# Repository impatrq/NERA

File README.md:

# N.E.R.A.

### Neuro Estimulación de Relajación Asistida

**Sistema de asistencia para la relajación mediante campos electromagnéticos pulsados (PEMF).**

=======
N.E.R.A.
Neuro Estimulación de Relajación Asistida
Sistema de asistencia para la relajación mediante campos electromagnéticos pulsados (PEMF).

N.E.R.A. - Sistema de asistencia para la relajación

¿Qué es N.E.R.A.?
N.E.R.A. es un dispositivo portátil en desarrollo, diseñado para explorar el uso de campos electromagnéticos pulsados (PEMF) como herramienta de apoyo para la relajación y el manejo del estrés.

El proyecto está orientado principalmente a personas que experimentan situaciones de estrés, sobrecarga mental o tensión. También se contemplan posibles aplicaciones relacionadas con el descanso y la recuperación física.

La propuesta consiste en integrar una vincha con bobinas electromagnéticas, un sistema electrónico de control y un reloj encargado del monitoreo. Estos componentes conforman un sistema que busca utilizar la información obtenida durante el monitoreo para gestionar el funcionamiento de la estimulación.

El desarrollo combina electrónica, programación y diseño mecánico con el objetivo de crear un dispositivo portátil, compacto y no invasivo.

## ¿Qué es N.E.R.A.?

N.E.R.A. es un dispositivo portátil en desarrollo, diseñado para explorar el uso de campos electromagnéticos pulsados (PEMF) como herramienta de apoyo para la relajación y el manejo del estrés.

El proyecto está orientado principalmente a personas que experimentan situaciones de estrés, sobrecarga mental o tensión. También se contemplan posibles aplicaciones relacionadas con el descanso y la recuperación física.

La propuesta consiste en integrar una vincha con bobinas electromagnéticas, un sistema electrónico de control y un reloj encargado del monitoreo. Estos componentes conforman un sistema que busca utilizar la información obtenida durante el monitoreo para gestionar el funcionamiento de la estimulación.

El desarrollo combina electrónica, programación y diseño mecánico con el objetivo de crear un dispositivo portátil, compacto y no invasivo.
=======
¿Cómo funciona?
El funcionamiento de N.E.R.A. se basa en la generación de campos electromagnéticos pulsados mediante bobinas.

El reloj realiza el monitoreo y se comunica con el microcontrolador ubicado en la vincha. El microcontrolador procesa la información recibida y gestiona el funcionamiento del sistema PEMF.

Cuando circula corriente eléctrica por las bobinas, se genera un campo magnético. Al modificar la corriente, el campo magnético también varía, produciendo pulsos electromagnéticos.

## ¿Cómo funciona?

El funcionamiento de N.E.R.A. se basa en la generación de campos electromagnéticos pulsados mediante bobinas.

El reloj realiza el monitoreo y se comunica con el microcontrolador ubicado en la vincha. El microcontrolador procesa la información recibida y gestiona el funcionamiento del sistema PEMF.

Cuando circula corriente eléctrica por las bobinas, se genera un campo magnético. Al modificar la corriente, el campo magnético también varía, produciendo pulsos electromagnéticos.

Las bobinas se encuentran ubicadas detrás de las orejas y forman parte del sistema de estimulación de la vincha.

El objetivo del proyecto es explorar la utilización de esta tecnología como herramienta de apoyo para favorecer la relajación y contribuir al bienestar del usuario.

---

## Arquitectura del sistema

N.E.R.A. está compuesto por diferentes módulos que trabajan de manera conjunta.

### 1. N.E.R.A. Headband — Vincha PEMF

=======
Las bobinas se encuentran ubicadas detrás de las orejas y forman parte del sistema de estimulación de la vincha.

El objetivo del proyecto es explorar la utilización de esta tecnología como herramienta de apoyo para favorecer la relajación y contribuir al bienestar del usuario.

Arquitectura del sistema
N.E.R.A. está compuesto por diferentes módulos que trabajan de manera conjunta.

1. N.E.R.A. Headband — Vincha PEMF

La vincha es el componente encargado de aplicar la estimulación electromagnética.

Incorpora dos bobinas rectangulares ubicadas detrás de las orejas y el microcontrolador encargado de gestionar el sistema.

Las bobinas generan campos magnéticos pulsados a partir de las señales eléctricas proporcionadas por el circuito de control.

El diseño mecánico contempla una estructura que permite alojar las bobinas y proteger los componentes electrónicos, manteniendo un formato portátil.

<<<<<<< Updated upstream

---

### 2. N.E.R.A. Watch — Sistema de monitoreo

=======
N.E.R.A. Headband

2. N.E.R.A. Watch — Sistema de monitoreo

El reloj es el componente destinado al monitoreo del usuario.

Su función dentro del proyecto es proporcionar información al sistema para permitir la gestión de la estimulación.

El reloj funciona de manera independiente de la vincha y cuenta con su propia alimentación eléctrica.

La comunicación entre el reloj y el microcontrolador de la vincha permite coordinar el funcionamiento de los distintos componentes del sistema.

---

### 3. Sistema PEMF

=======
N.E.R.A. Watch

3. Sistema PEMF

El sistema PEMF está compuesto principalmente por las bobinas y la electrónica necesaria para controlar su funcionamiento.

Las bobinas reciben señales eléctricas controladas por el sistema electrónico y generan campos electromagnéticos pulsados.

El sistema está diseñado para funcionar de forma no invasiva y se encuentra integrado físicamente en la vincha.

---

## Tecnología PEMF

PEMF (*Pulsed Electromagnetic Fields*) es una tecnología basada en la generación de campos electromagnéticos que varían mediante pulsos.
=======
Bobinas del sistema PEMF

Tecnología PEMF
PEMF (Pulsed Electromagnetic Fields) es una tecnología basada en la generación de campos electromagnéticos que varían mediante pulsos.

Su funcionamiento se relaciona con el principio de inducción electromagnética: cuando una corriente eléctrica circula por una bobina, genera un campo magnético. Al modificar esa corriente, el campo magnético también cambia.

La investigación sobre PEMF estudia la interacción de estos campos con los tejidos biológicos y sus posibles efectos en determinados procesos celulares.

Existen investigaciones sobre diferentes aplicaciones de esta tecnología, aunque sus efectos dependen de las características de la señal, la intensidad, la frecuencia y la aplicación estudiada.

En N.E.R.A., esta tecnología se utiliza como base para desarrollar un dispositivo orientado principalmente a la relajación y el manejo del estrés. Su eficacia para estos fines deberá evaluarse mediante pruebas específicas.

---

## Objetivos del proyecto

=======
Objetivos del proyecto

El objetivo principal de N.E.R.A. es desarrollar un dispositivo portátil que permita explorar la aplicación de campos electromagnéticos pulsados como herramienta de apoyo para la relajación.

Entre sus objetivos específicos se encuentran:

* Desarrollar un sistema PEMF compacto y portátil.
* Integrar la generación de campos electromagnéticos pulsados en una vincha.
* Implementar un sistema electrónico capaz de controlar el funcionamiento de las bobinas.
* Integrar un sistema de monitoreo mediante un reloj.
* Establecer comunicación entre el reloj y la electrónica de la vincha.
* Diseñar carcasas y soportes que permitan alojar y proteger los componentes.
* Fabricar prototipos mediante impresión 3D.
* Investigar las posibilidades de aplicación de la tecnología PEMF en el bienestar y la relajación.

---

## Desarrollo tecnológico

El proyecto integra distintas áreas de la ingeniería y el desarrollo tecnológico.

| Área            | Desarrollo                                                         |
| --------------- | ------------------------------------------------------------------ |
| Electrónica     | Diseño de circuitos, selección de componentes y desarrollo de PCB. |
| Firmware        | Programación del microcontrolador y control del sistema.           |
| Diseño mecánico | Modelado 3D de carcasas, soportes y alojamientos para las bobinas. |
| Impresión 3D    | Fabricación de piezas para el ensamblaje del dispositivo.          |
| Integración     | Conexión y coordinación de los diferentes módulos del sistema.     |

### Electrónica

=======
Desarrollar un sistema PEMF compacto y portátil.
Integrar la generación de campos electromagnéticos pulsados en una vincha.
Implementar un sistema electrónico capaz de controlar el funcionamiento de las bobinas.
Integrar un sistema de monitoreo mediante un reloj.
Establecer comunicación entre el reloj y la electrónica de la vincha.
Diseñar carcasas y soportes que permitan alojar y proteger los componentes.
Fabricar prototipos mediante impresión 3D.
Investigar las posibilidades de aplicación de la tecnología PEMF en el bienestar y la relajación.
Desarrollo tecnológico
El proyecto integra distintas áreas de la ingeniería y el desarrollo tecnológico.

Área	Desarrollo
Electrónica	Diseño de circuitos, selección de componentes y desarrollo de PCB.
Firmware	Programación del microcontrolador y control del sistema.
Diseño mecánico	Modelado 3D de carcasas, soportes y alojamientos para las bobinas.
Impresión 3D	Fabricación de piezas para el ensamblaje del dispositivo.
Integración	Conexión y coordinación de los diferentes módulos del sistema.
Electrónica

El diseño electrónico contempla una placa de circuito impreso que integra el microcontrolador y los componentes necesarios para controlar el sistema.

La distribución de los componentes y las conexiones se plantea teniendo en cuenta el tamaño del dispositivo, la alimentación y la disposición de las bobinas.

### Diseño mecánico

=======
PCB del sistema N.E.R.A.

Diseño mecánico

El diseño mecánico se centra en desarrollar una estructura que permita integrar los componentes de manera compacta y segura.

Se trabaja en el modelado de las carcasas de la placa electrónica, los alojamientos de las bobinas, separadores y soportes necesarios para el ensamblaje.

Las piezas se diseñan considerando su fabricación mediante impresión 3D.

---

## Tecnologías y herramientas

Las principales tecnologías y herramientas utilizadas en el desarrollo incluyen:

* **ESP32:** microcontrolador utilizado para gestionar el sistema electrónico.
* **C/C++:** programación del firmware.
* **Diseño de PCB:** desarrollo de circuitos electrónicos.
* **Blender:** modelado tridimensional de componentes y carcasas.
* **Impresión 3D:** fabricación de piezas mecánicas y prototipos.
* **GitHub:** almacenamiento, organización y seguimiento del desarrollo del proyecto.

---

## Estructura del repositorio

El repositorio está organizado para separar los distintos componentes del proyecto y facilitar su desarrollo.

| Directorio    | Contenido                                                |
| ------------- | -------------------------------------------------------- |
| `docs/`       | Documentación técnica, imágenes e informes del proyecto. |
| `firmware/`   | Código fuente y programas del microcontrolador.          |
| `hardware/`   | Esquemáticos, circuitos y diseños de PCB.                |
| `mechanical/` | Modelos 3D, carcasas, soportes y diseños mecánicos.      |

---

## Estado del proyecto

**En desarrollo.**
=======
Diseño mecánico de N.E.R.A.

Tecnologías y herramientas
Las principales tecnologías y herramientas utilizadas en el desarrollo incluyen:

ESP32: microcontrolador utilizado para gestionar el sistema electrónico.
C/C++: programación del firmware.
Diseño de PCB: desarrollo de circuitos electrónicos.
Blender: modelado tridimensional de componentes y carcasas.
Impresión 3D: fabricación de piezas mecánicas y prototipos.
GitHub: almacenamiento, organización y seguimiento del desarrollo del proyecto.
Estructura del repositorio
El repositorio está organizado para separar los distintos componentes del proyecto y facilitar su desarrollo.

Directorio	Contenido
docs/	Documentación técnica, imágenes e informes del proyecto.
firmware/	Código fuente y programas del microcontrolador.
hardware/	Esquemáticos, circuitos y diseños de PCB.
mechanical/	Modelos 3D, carcasas, soportes y diseños mecánicos.
Estado del proyecto
En desarrollo.

N.E.R.A. se encuentra en una etapa de diseño, desarrollo e integración de sus componentes electrónicos y mecánicos.

El proyecto contempla el desarrollo de prototipos, la integración de los sistemas y la realización de pruebas para evaluar su funcionamiento.

Las funcionalidades y aplicaciones previstas se irán documentando a medida que sean implementadas y validadas.

---

## Aplicaciones previstas

=======
Aplicaciones previstas

El proyecto se centra principalmente en investigar el uso de la tecnología PEMF como posible herramienta complementaria para favorecer la relajación y el bienestar.

También se consideran posibles aplicaciones relacionadas con el descanso y la recuperación física, incluidos contextos deportivos.

Estas aplicaciones forman parte de los objetivos de investigación y desarrollo del proyecto. N.E.R.A. no está validado como tratamiento para trastornos de salud mental ni sustituye la atención profesional.

---

## Institución

**Escuela de Educación Secundaria Técnica N.º 7 «Taller Regional Quilmes»**

Buenos Aires, Argentina.

**Proyecto:** N.E.R.A.
**Significado:** Neuro Estimulación de Relajación Asistida
**Área:** Aviónica y desarrollo tecnológico.

---

<p align="center">
  <strong>N.E.R.A. — Neuro Estimulación de Relajación Asistida.</strong>
</p>
=======
Institución
Escuela de Educación Secundaria Técnica N.º 7 «Taller Regional Quilmes»

Buenos Aires, Argentina.

Proyecto: N.E.R.A. Significado: Neuro Estimulación de Relajación Asistida Área: Aviónica y desarrollo tecnológico.

N.E.R.A. — Neuro Estimulación de Relajación Asistida.
>>>>>>> Stashed changes

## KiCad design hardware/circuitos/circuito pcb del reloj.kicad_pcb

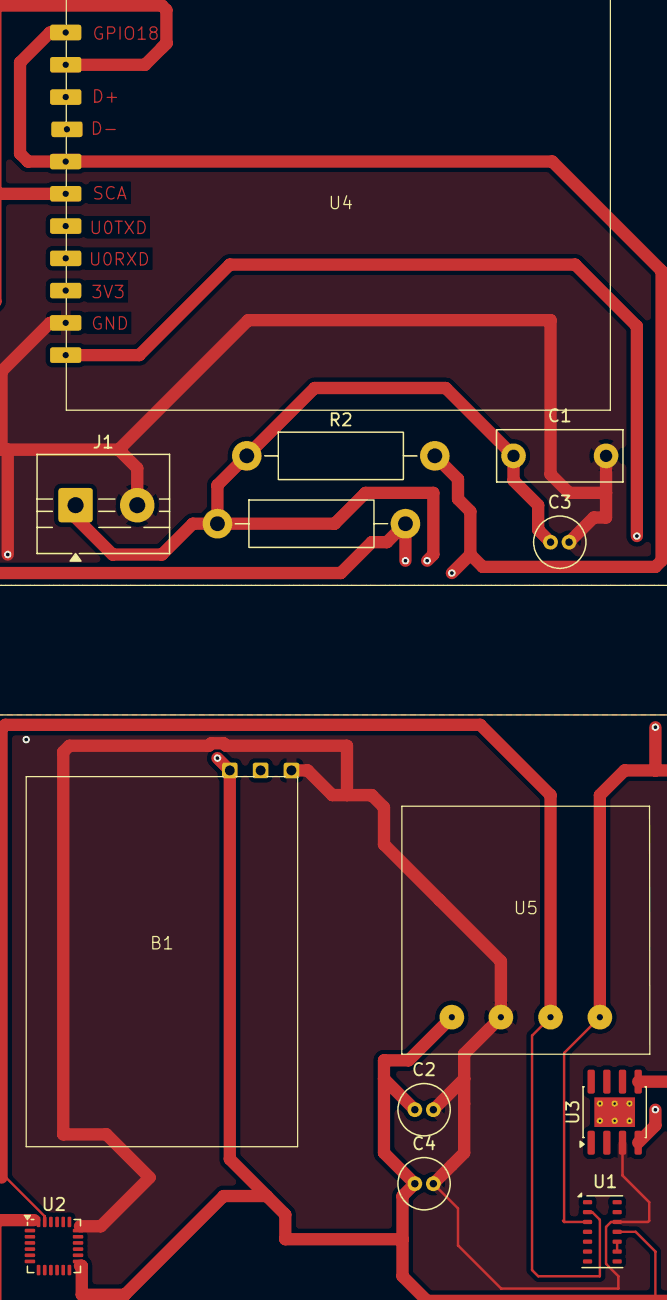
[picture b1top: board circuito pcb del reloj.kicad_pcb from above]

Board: 2 copper layers, 13 parts (0 on the bottom side), 6 nets.

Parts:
B1: batman 51
C1: 10uF; C_Rect_L10.0mm_W4.0mm_P7.50mm_FKS3_FKP3
C2, C3, C4: 100nF; C_Radial_D4.0mm_H5.0mm_P1.50mm
J1: Screw_Terminal_01x02; TerminalBlock_MaiXu_MX126-5.0-02P_1x02_P5.00mm
R1, R2: 4,7K; R_Axial_DIN0411_L9.9mm_D3.6mm_P15.24mm_Horizontal
U1: MAX30102; Maxim_OLGA-14_3.3x5.6mm_P0.8mm
U2: MPU-6050; InvenSense_QFN-24_4x4mm_P0.5mm
U3: TP4056-42-ESOP8; SOIC-8-1EP_3.9x4.9mm_P1.27mm_EP2.41x3.3mm_ThermalVias
U4: ESP32_C6
U5: Tito

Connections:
5v: U3.4 (V_{CC}), U4.11 (5V)
unnamed: U1.9 (VLED+), U1.10 (VLED+)
clock: R2.2, U1.2 (SCL), U2.23 (SCL), U4.1 (GPIO18), U4.5 (SCL), U5.3 (SCL)
dat sensor: R1.2, U1.3 (SDA), U2.24 (SDA), U4.2 (GPIO9), U4.6 (SDA), U5.4 (SDA)
prime: B1.1 (VCC), C1.1, C2.1, C3.1, C4.1, J1.1, R1.1, R2.1, U1.11 (VDD), U2.13 (VDD), U3.5 (BAT), U5.1 (VIN)
tierra: B1.3 (GND), C1.2, C2.2, C3.2, C4.2, J1.2, U1.12 (GND), U2.18 (GND), U3.3 (GND), U4.10 (GND), U5.2 (GND)

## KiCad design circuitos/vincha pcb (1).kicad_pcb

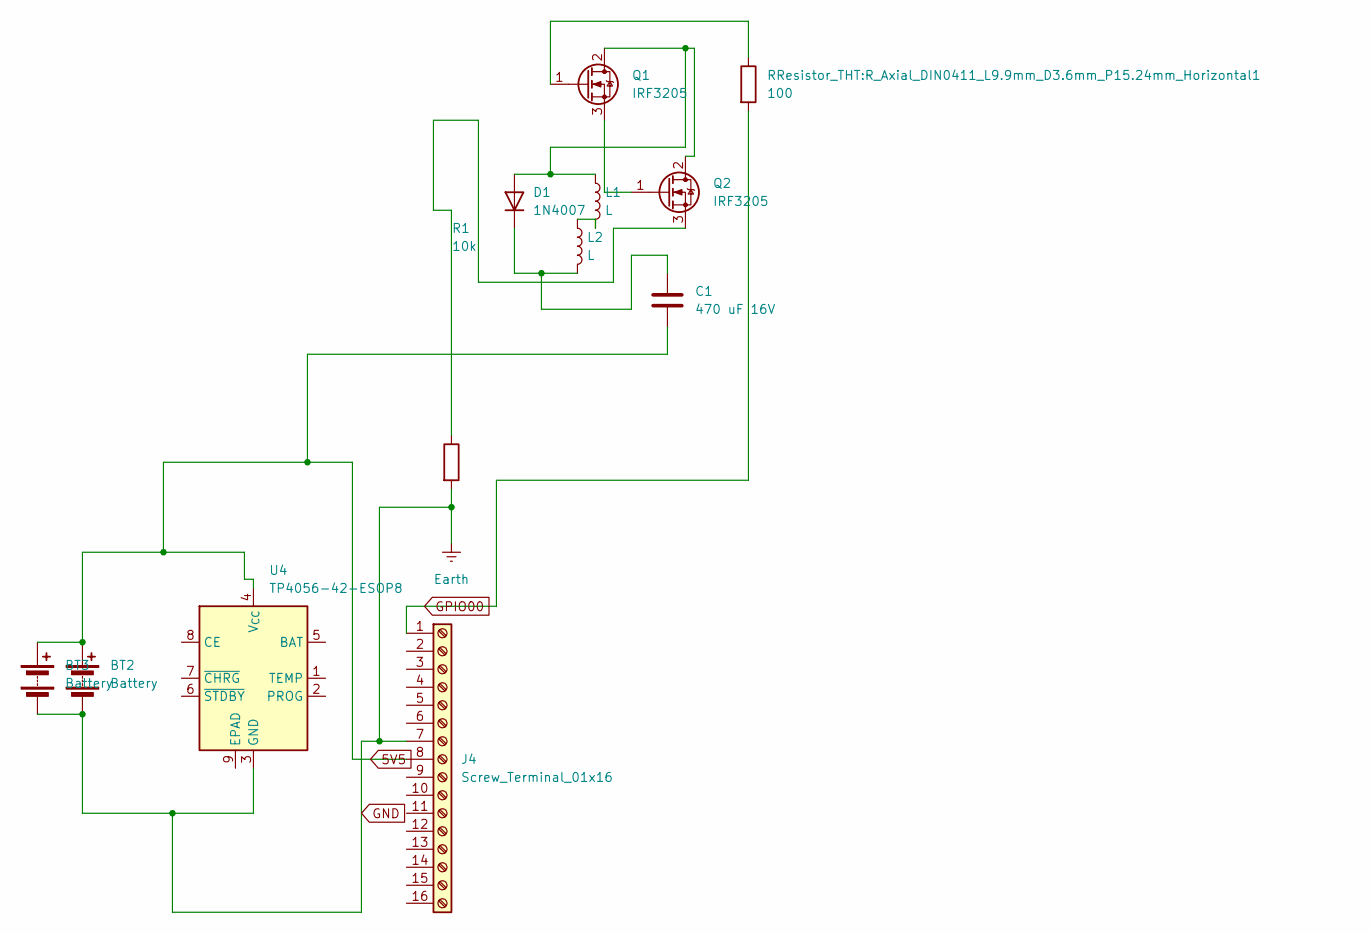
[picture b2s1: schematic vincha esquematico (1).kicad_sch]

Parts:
BT2, BT3: Battery; bateria escopeta
C1: 470 uF 16V; CP_EIA-6032-15_Kemet-U
D1: 1N4007; D_DO-41_SOD81_P10.16mm_Horizontal
J4: Screw_Terminal_01x16; Nera (2)
L1, L2: L; inductor pemf
Q1, Q2: IRF3205; TO-220-3_Vertical
R1: 10k; R_Axial_DIN0411_L9.9mm_D3.6mm_P15.24mm_Horizontal
RResistor_THT:R_Axial_DIN0411_L9.9mm_D3.6mm_P15.24mm_Horizontal1: 100; R_Axial_DIN0411_L9.9mm_D3.6mm_P15.24mm_Horizontal
U4: TP4056-42-ESOP8; SOIC-8-1EP_3.9x4.9mm_P1.27mm_EP2.41x3.3mm_ThermalVias

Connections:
5V5: BT2.1 (+), BT3.1 (+), C1.2, J4.8, U4.4 (V_{CC})
GND: BT2.2 (-), BT3.2 (-), J4.7, R1.2, U4.3 (GND)
GPIO00: J4.1, RResistor_THT:R_Axial_DIN0411_L9.9mm_D3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.2
unnamed: D1.2 (A), L1.1, Q1.2 (D), Q2.2 (D)
unnamed: C1.1, D1.1 (K), L2.2
unnamed: L1.2, L2.1
unnamed: Q1.1 (G), RResistor_THT:R_Axial_DIN0411_L9.9mm_D3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.1
unnamed: Q1.3 (S), Q2.1 (G)
unnamed: Q2.3 (S), R1.1

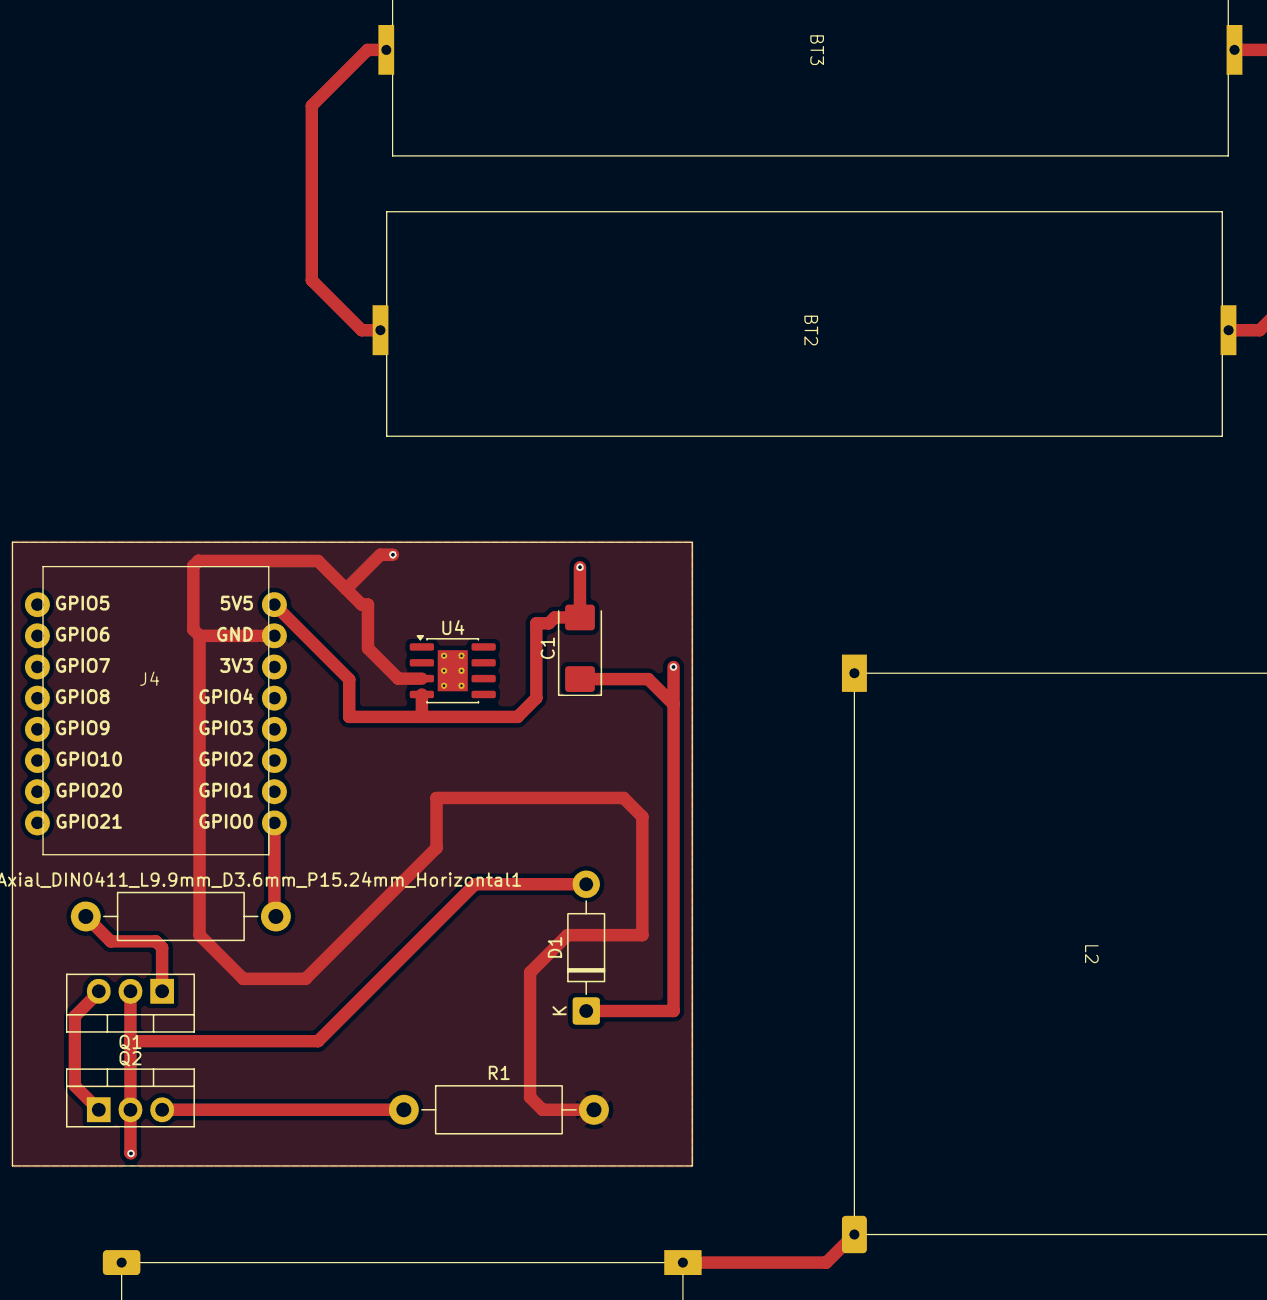
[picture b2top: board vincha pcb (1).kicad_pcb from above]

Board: 2 copper layers, 12 parts (0 on the bottom side), 9 nets.

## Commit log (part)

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2026-05-14 Anteproyecto
2026-06-23 Imagenes de la App
    Primeras imagenes de como se ve la app
